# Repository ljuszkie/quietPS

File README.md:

# quietPS 
Quiet power supply for tube preamplifiers. Project was
created in KiCad BZR 5054 on Linux, verified to be editable in KiCad
4.0.2, which is target version (switch to new version soon). Board
view image and pdf schematic can be found in preview folder.

Nieskoszumny zasilacz do przedwzmacniaczy lampowych. Projekt utworzony
w KiCadzie BZR 5054 na Linuksie, można go edytować w KiCadzie 4.0.2,
który jest docelową wersją (przejście na nową wersję wkrótce). Obrazek
z widokiem płytki i schemat w formacie pdf znajdują się w folderze
preview.

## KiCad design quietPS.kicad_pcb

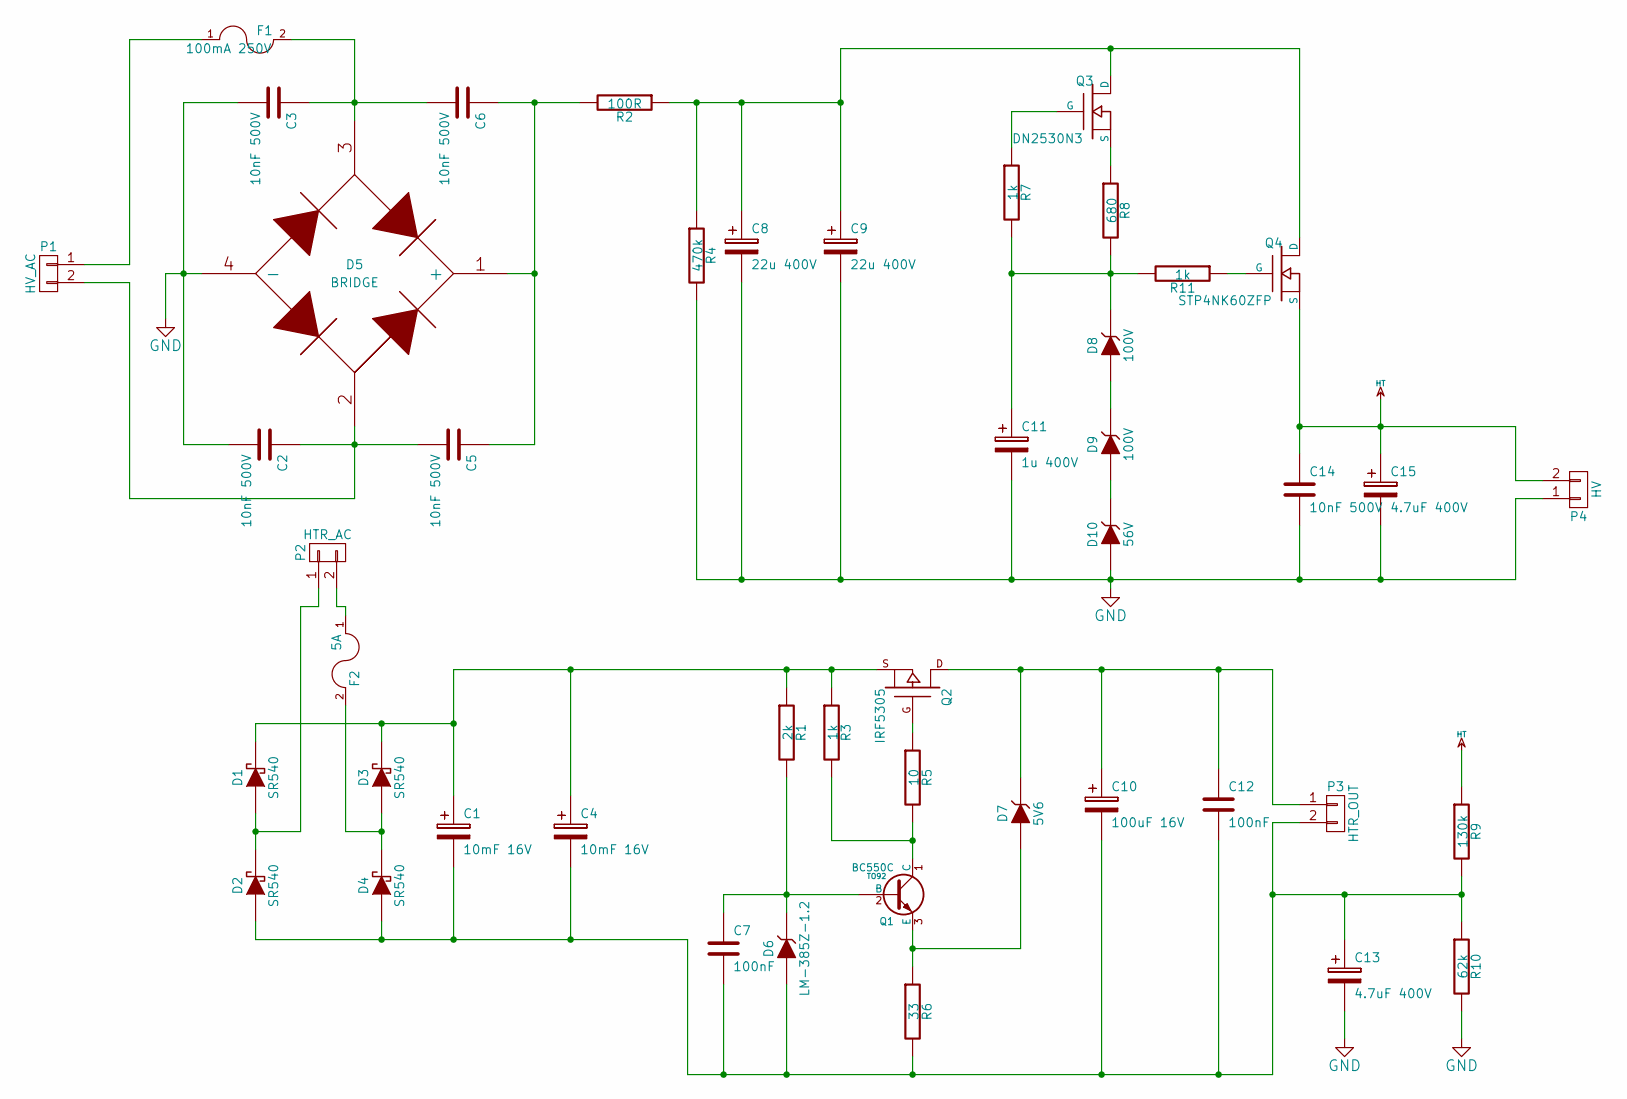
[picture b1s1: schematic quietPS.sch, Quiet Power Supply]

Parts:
C1, C4: 10mF 16V
C2, C3, C5, C6, C14: 10nF 500V
C7, C12: 100nF
C8, C9: 22u 400V
C10: 100uF 16V
C11: 1u 400V
C13, C15: 4.7uF 400V
D1, D2, D3, D4: SR540
D5: BRIDGE
D6: LM-385Z-1.2
D7: 5V6
D8, D9: 100V
D10: 56V
F1: 100mA 250V
F2: 5A
P1: HV_AC
P2: HTR_AC
P3: HTR_OUT
P4: HV
Q1: BC550C; TO92
Q2: IRF5305
Q3: DN2530N3
Q4: STP4NK60ZFP
R1: 2k
R2: 100R
R3, R7, R11: 1k
R4: 470k
R5: 10
R6: 33
R8: 680
R9: 130k
R10: 62k

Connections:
GND: C2.2, C3.2, C8.2, C9.2, C11.2, C13.2, C14.2, C15.2, D5.4 (-), D10.1 (A), P4.1, R4.2, R10.2
HT: C14.1, C15.1, P4.2, Q4.S, R9.1
unnamed: C1.1, C4.1, D1.2 (K), D3.2 (K), Q2.S, R1.1, R3.1
unnamed: C1.2, C4.2, C7.2, C10.2, C12.2, C13.1, D2.1 (A), D4.1 (A), D6.3 (A), P3.2, R6.2, R9.2, R10.1
unnamed: C2.1, C5.2, D5.2, P1.2
unnamed: C3.1, C6.2, D5.3, F1.2
unnamed: C5.1, C6.1, D5.1 (+), R2.2
unnamed: C7.1, D6.2 (K), Q1.2 (B), R1.2
unnamed: C8.1, C9.1, Q3.D, Q4.D, R2.1, R4.1
unnamed: C10.1, C12.1, D7.2 (K), P3.1, Q2.D
unnamed: C11.1, D8.2 (K), R7.2, R8.2, R11.2
unnamed: D1.1 (A), D2.2 (K), P2.1
unnamed: D3.1 (A), D4.2 (K), F2.2
unnamed: D7.1 (A), Q1.3 (E), R6.1
unnamed: D8.1 (A), D9.2 (K)
unnamed: D9.1 (A), D10.2 (K)
unnamed: F1.1, P1.1
unnamed: F2.1, P2.2
unnamed: Q1.1 (C), R3.2, R5.2
unnamed: Q2.G, R5.1
unnamed: Q3.G, R7.1
unnamed: Q3.S, R8.1
unnamed: Q4.G, R11.1

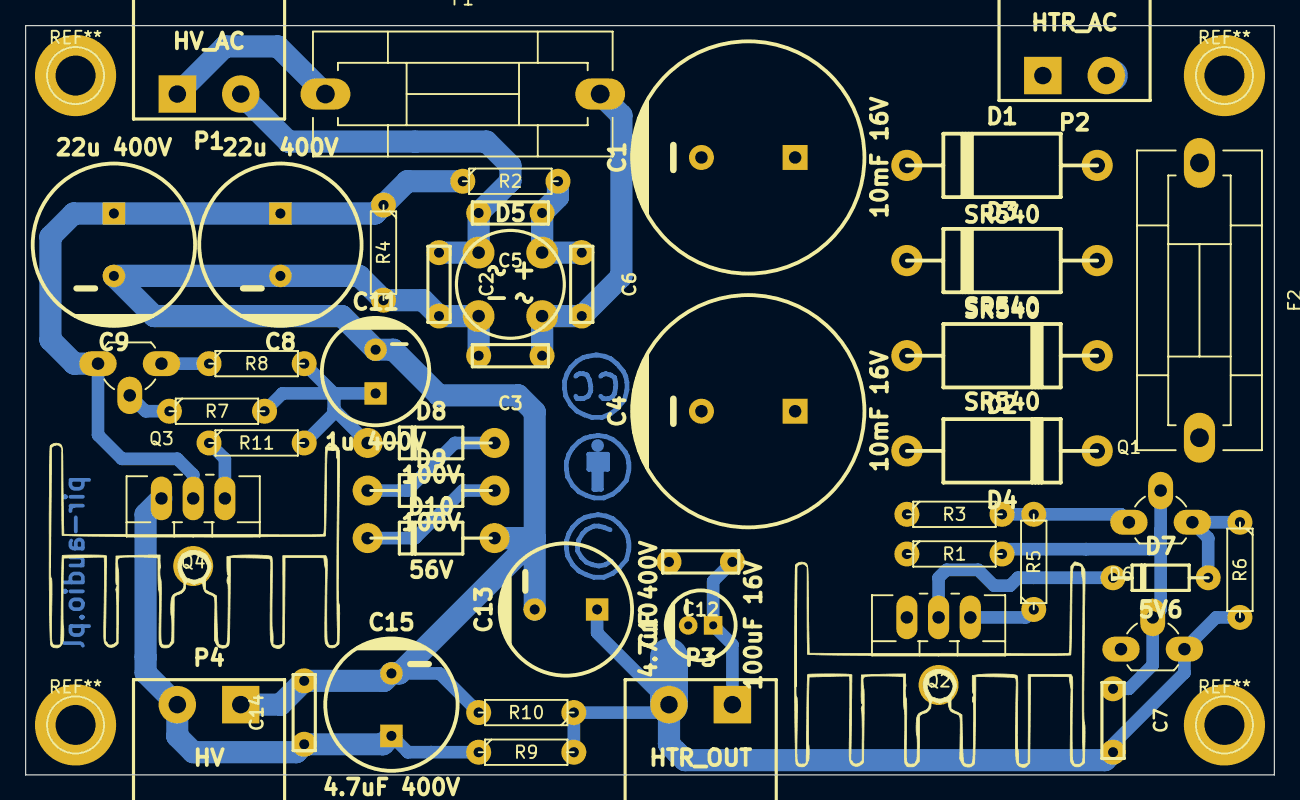
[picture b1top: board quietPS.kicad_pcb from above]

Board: 2 copper layers, 100.0 x 60.0 mm, 46 parts (0 on the bottom side), 23 nets.

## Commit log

2016-09-11 Project files added
2016-09-11 Project files added, preview added, README updated

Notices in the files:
quietPS.kicad_pcb:
licensed under CC BY SA 4.0 International
quietPS.sch:
https://creativecommons.org/licenses/by-sa/4.0
